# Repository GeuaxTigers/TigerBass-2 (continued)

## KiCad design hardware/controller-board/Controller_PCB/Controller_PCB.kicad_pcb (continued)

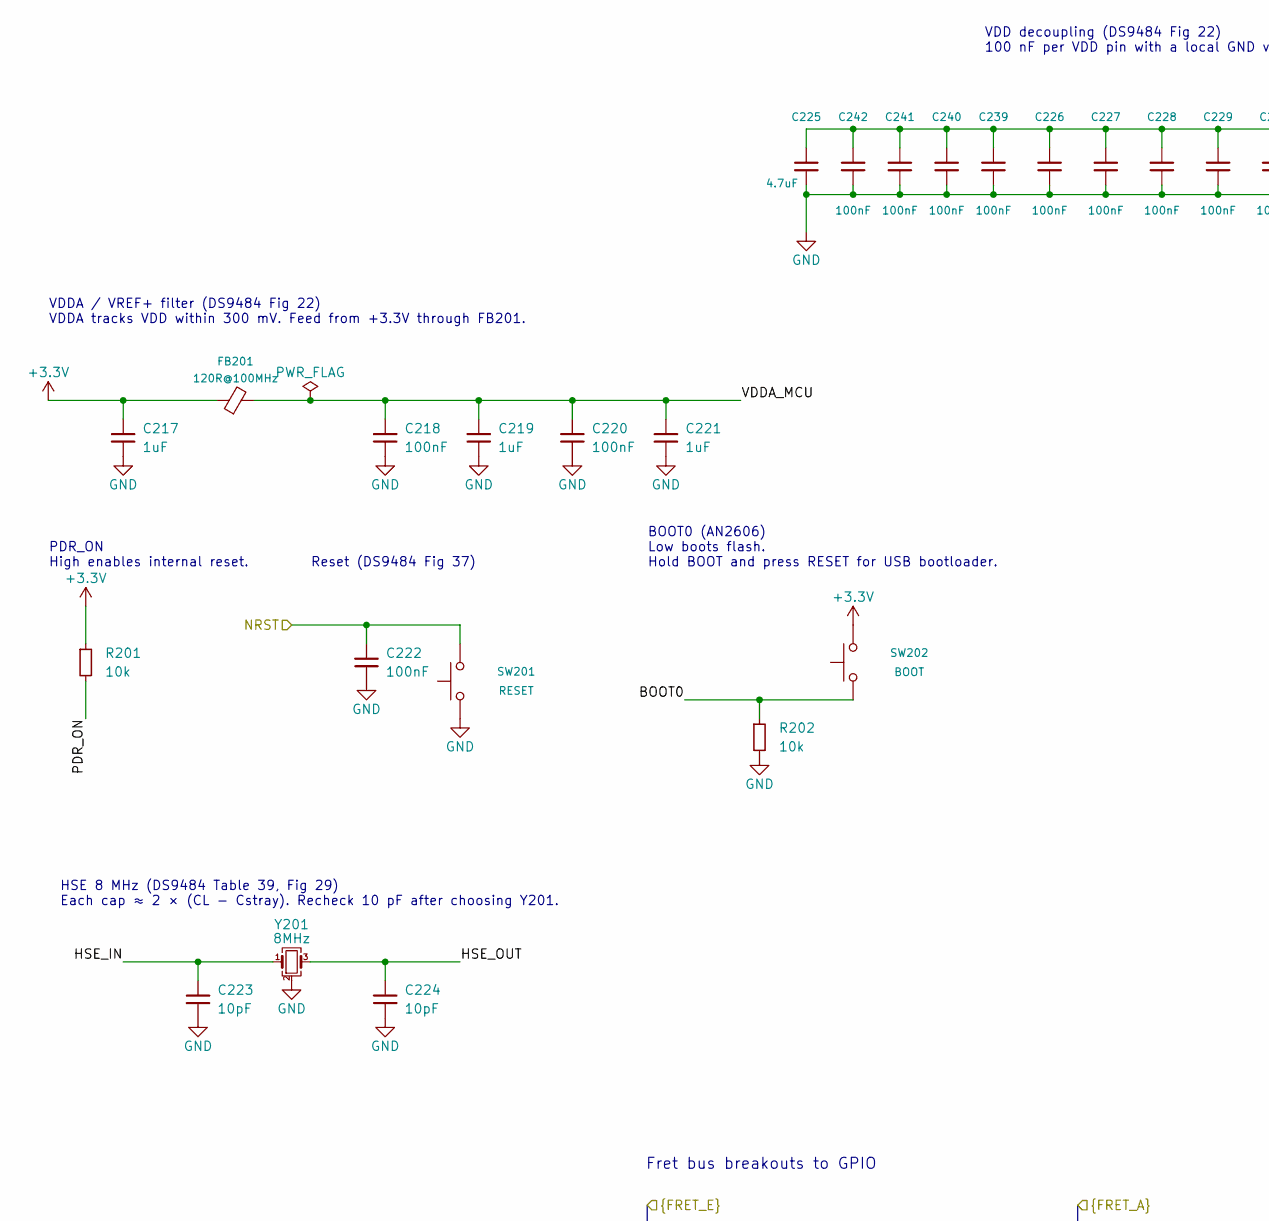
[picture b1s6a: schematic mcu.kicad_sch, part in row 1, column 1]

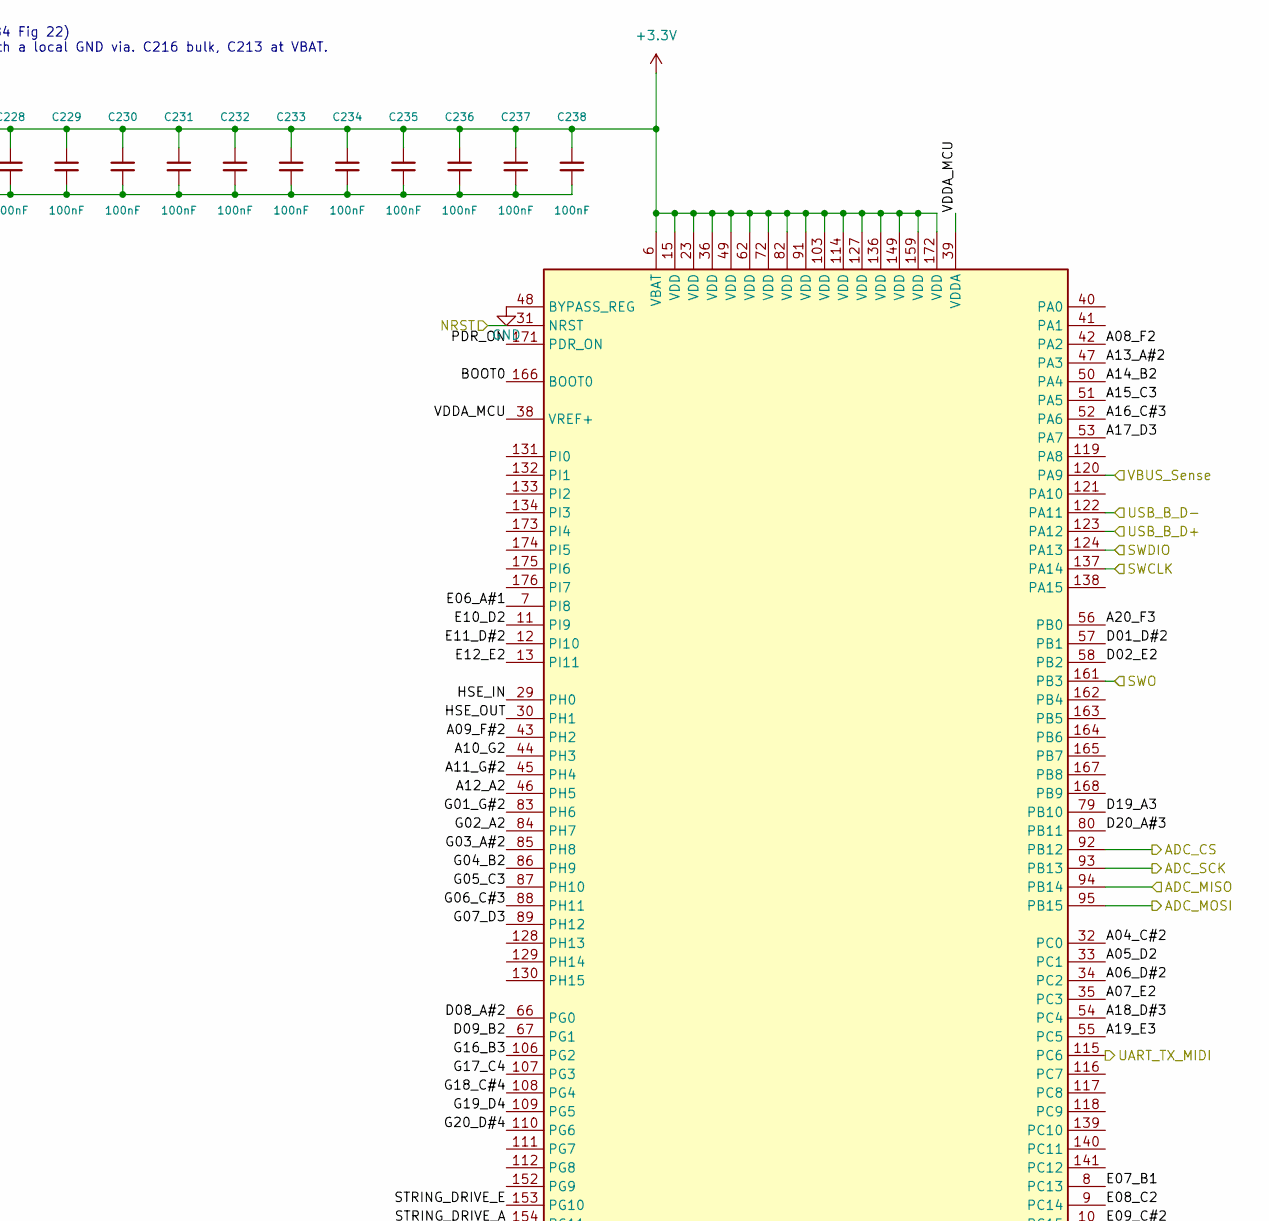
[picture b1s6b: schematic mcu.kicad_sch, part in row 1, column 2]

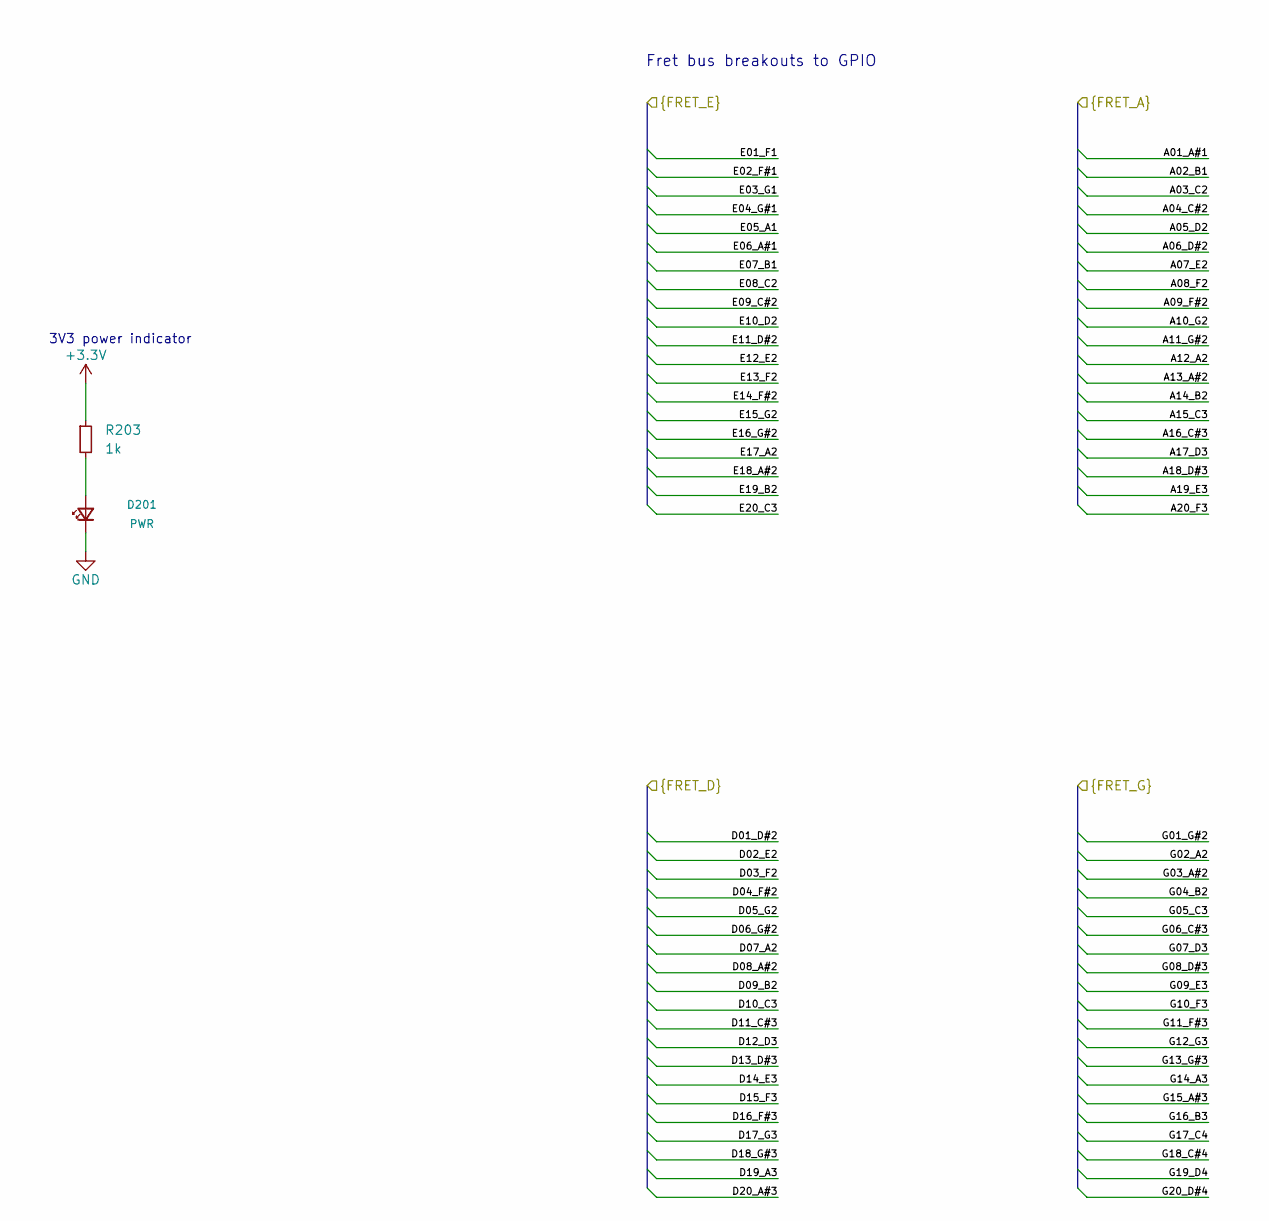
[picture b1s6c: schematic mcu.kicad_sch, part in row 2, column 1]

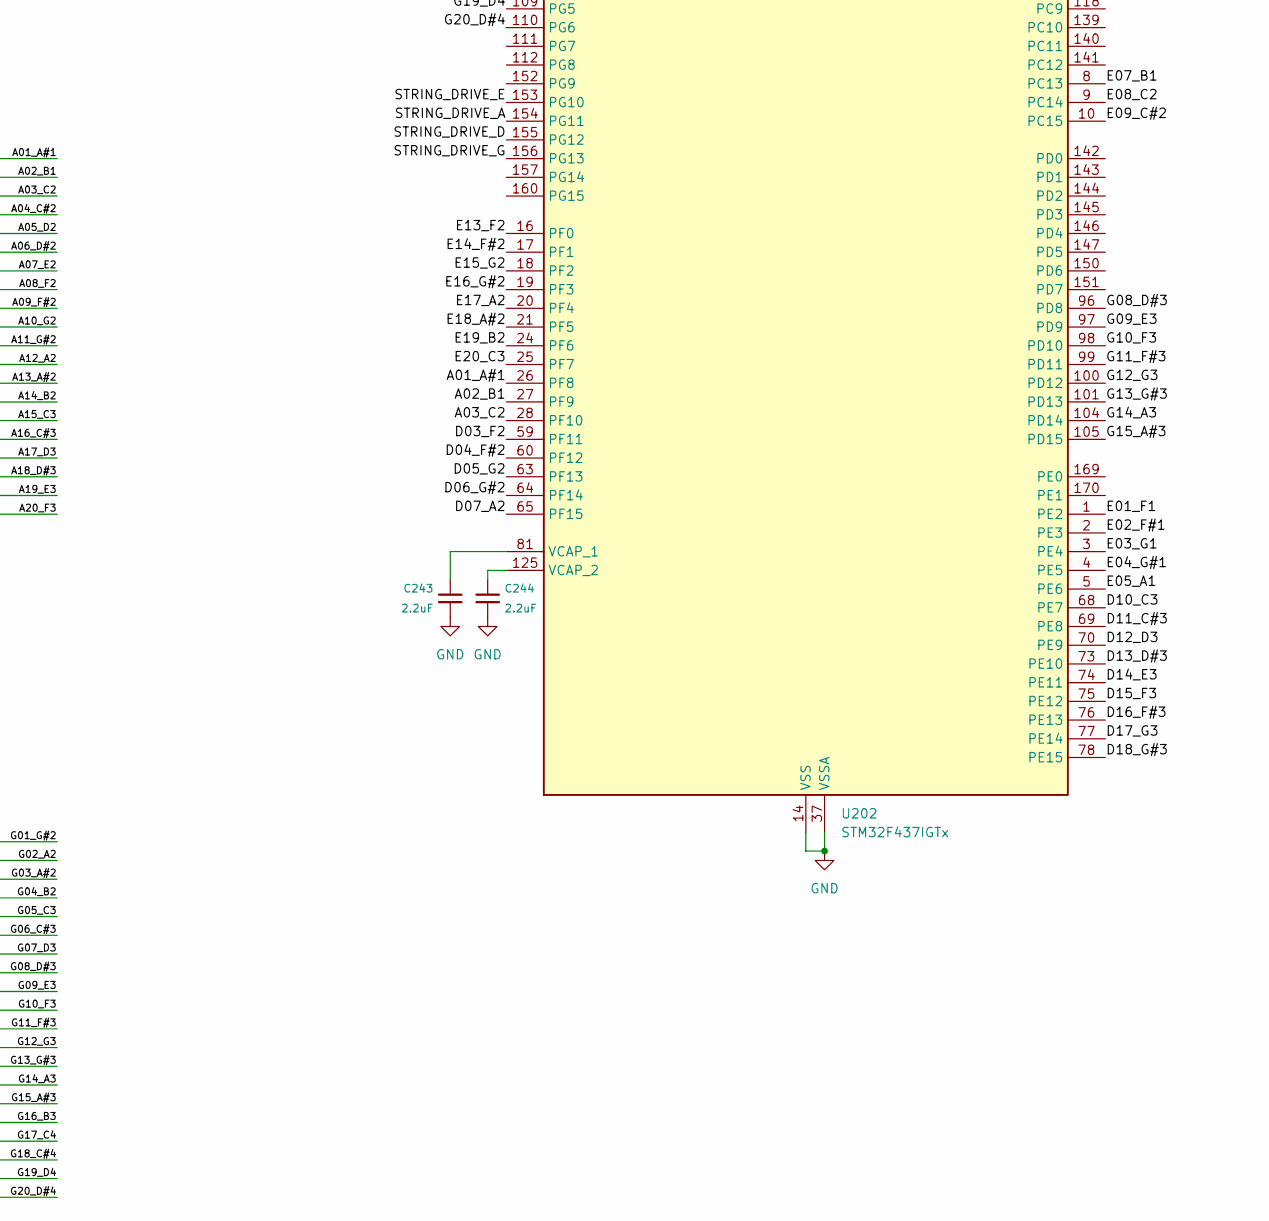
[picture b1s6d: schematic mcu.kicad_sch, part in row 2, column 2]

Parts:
C217, C219, C221: 1uF; C_0603_1608Metric
C218, C220, C222, C226, C227, C228, C229, C230, C231, C232, C233, C234, C235, C236, C237, C238, C239, C240, C241, C242: 100nF; C_0603_1608Metric
C223, C224: 10pF; C_0603_1608Metric
C225: 4.7uF; C_0603_1608Metric
C243, C244: 2.2uF; C_0603_1608Metric
D201: PWR; LED_0603_1608Metric
FB201: 120R@100MHz; L_0603_1608Metric
R201, R202: 10k; R_0603_1608Metric
R203: 1k; R_0603_1608Metric
SW201: RESET; SW_SPST_TL3342
SW202: BOOT; SW_SPST_TL3342
U202: STM32F437IGTx; LQFP-176_24x24mm_P0.5mm
Y201: 8MHz; Crystal_SMD_3225-4Pin_3.2x2.5mm

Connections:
+3.3V: C217.1, C225.1, C226.1, C227.1, C228.1, C229.1, C230.1, C231.1, C232.1, C233.1, C234.1, C235.1, C236.1, C237.1, C238.1, C239.1, C240.1, C241.1, C242.1, FB201.1, R201.1, R203.1, SW202.2, U202.6 (VBAT), U202.15 (VDD), U202.23 (VDD), U202.36 (VDD), U202.49 (VDD), U202.62 (VDD), U202.72 (VDD), U202.82 (VDD), U202.91 (VDD), U202.103 (VDD), U202.114 (VDD), U202.127 (VDD), U202.136 (VDD), U202.149 (VDD), U202.159 (VDD), U202.172 (VDD); also elsewhere on the board
/A01_A#1: U202.26 (PF8); also elsewhere on the board
/A02_B1: U202.27 (PF9); also elsewhere on the board
/A03_C2: U202.28 (PF10); also elsewhere on the board
/A04_C#2: U202.32 (PC0); also elsewhere on the board
/A05_D2: U202.33 (PC1); also elsewhere on the board
/A06_D#2: U202.34 (PC2); also elsewhere on the board
/A07_E2: U202.35 (PC3); also elsewhere on the board
/A08_F2: U202.42 (PA2); also elsewhere on the board
/A09_F#2: U202.43 (PH2); also elsewhere on the board
/A10_G2: U202.44 (PH3); also elsewhere on the board
/A11_G#2: U202.45 (PH4); also elsewhere on the board
/A12_A2: U202.46 (PH5); also elsewhere on the board
/A13_A#2: U202.47 (PA3); also elsewhere on the board
/A14_B2: U202.50 (PA4); also elsewhere on the board
/A15_C3: U202.51 (PA5); also elsewhere on the board
/A16_C#3: U202.52 (PA6); also elsewhere on the board
/A17_D3: U202.53 (PA7); also elsewhere on the board
/A18_D#3: U202.54 (PC4); also elsewhere on the board
/A19_E3: U202.55 (PC5); also elsewhere on the board
/A20_F3: U202.56 (PB0); also elsewhere on the board
/Amplitude Detection/ADC_CS: U202.92 (PB12)
/Amplitude Detection/ADC_MISO: U202.94 (PB14)
/Amplitude Detection/ADC_MOSI: U202.95 (PB15)
/Amplitude Detection/ADC_SCK: U202.93 (PB13)
/D01_D#2: U202.57 (PB1); also elsewhere on the board
/D02_E2: U202.58 (PB2); also elsewhere on the board
/D03_F2: U202.59 (PF11); also elsewhere on the board
/D04_F#2: U202.60 (PF12); also elsewhere on the board
/D05_G2: U202.63 (PF13); also elsewhere on the board
/D06_G#2: U202.64 (PF14); also elsewhere on the board
/D07_A2: U202.65 (PF15); also elsewhere on the board
/D08_A#2: U202.66 (PG0); also elsewhere on the board
/D09_B2: U202.67 (PG1); also elsewhere on the board
/D10_C3: U202.68 (PE7); also elsewhere on the board
/D11_C#3: U202.69 (PE8); also elsewhere on the board
/D12_D3: U202.70 (PE9); also elsewhere on the board
/D13_D#3: U202.73 (PE10); also elsewhere on the board
/D14_E3: U202.74 (PE11); also elsewhere on the board
/D15_F3: U202.75 (PE12); also elsewhere on the board
/D16_F#3: U202.76 (PE13); also elsewhere on the board
/D17_G3: U202.77 (PE14); also elsewhere on the board
/D18_G#3: U202.78 (PE15); also elsewhere on the board
/D19_A3: U202.79 (PB10); also elsewhere on the board
/D20_A#3: U202.80 (PB11); also elsewhere on the board
/E01_F1: U202.1 (PE2); also elsewhere on the board
/E02_F#1: U202.2 (PE3); also elsewhere on the board
/E03_G1: U202.3 (PE4); also elsewhere on the board
/E04_G#1: U202.4 (PE5); also elsewhere on the board
/E05_A1: U202.5 (PE6); also elsewhere on the board
/E06_A#1: U202.7 (PI8); also elsewhere on the board
/E07_B1: U202.8 (PC13); also elsewhere on the board
/E08_C2: U202.9 (PC14); also elsewhere on the board
/E09_C#2: U202.10 (PC15); also elsewhere on the board
/E10_D2: U202.11 (PI9); also elsewhere on the board
/E11_D#2: U202.12 (PI10); also elsewhere on the board
/E12_E2: U202.13 (PI11); also elsewhere on the board
/E13_F2: U202.16 (PF0); also elsewhere on the board
/E14_F#2: U202.17 (PF1); also elsewhere on the board
/E15_G2: U202.18 (PF2); also elsewhere on the board
/E16_G#2: U202.19 (PF3); also elsewhere on the board
/E17_A2: U202.20 (PF4); also elsewhere on the board
/E18_A#2: U202.21 (PF5); also elsewhere on the board
/E19_B2: U202.24 (PF6); also elsewhere on the board
/E20_C3: U202.25 (PF7); also elsewhere on the board
/G01_G#2: U202.83 (PH6); also elsewhere on the board
/G02_A2: U202.84 (PH7); also elsewhere on the board
/G03_A#2: U202.85 (PH8); also elsewhere on the board
/G04_B2: U202.86 (PH9); also elsewhere on the board
/G05_C3: U202.87 (PH10); also elsewhere on the board
/G06_C#3: U202.88 (PH11); also elsewhere on the board
/G07_D3: U202.89 (PH12); also elsewhere on the board
/G08_D#3: U202.96 (PD8); also elsewhere on the board
/G09_E3: U202.97 (PD9); also elsewhere on the board
/G10_F3: U202.98 (PD10); also elsewhere on the board
/G11_F#3: U202.99 (PD11); also elsewhere on the board
/G12_G3: U202.100 (PD12); also elsewhere on the board
/G13_G#3: U202.101 (PD13); also elsewhere on the board
/G14_A3: U202.104 (PD14); also elsewhere on the board
/G15_A#3: U202.105 (PD15); also elsewhere on the board
/G16_B3: U202.106 (PG2); also elsewhere on the board
/G17_C4: U202.107 (PG3); also elsewhere on the board
/G18_C#4: U202.108 (PG4); also elsewhere on the board
/G19_D4: U202.109 (PG5); also elsewhere on the board
/G20_D#4: U202.110 (PG6); also elsewhere on the board
/MCU/BOOT0: R202.1, SW202.1, U202.166 (BOOT0)
/MCU/HSE_IN: C223.1, U202.29 (PH0), Y201.1
/MCU/HSE_OUT: C224.1, U202.30 (PH1), Y201.3
/MCU/PDR_ON: R201.2, U202.171 (PDR_ON)
/MCU/STRING_DRIVE_A: U202.154 (PG11)
/MCU/STRING_DRIVE_D: U202.155 (PG12)
/MCU/STRING_DRIVE_E: U202.153 (PG10)
/MCU/STRING_DRIVE_G: U202.156 (PG13)
/MCU/VDDA_MCU: C218.1, C219.1, C220.1, C221.1, FB201.2, U202.38 (VREF+), U202.39 (VDDA)
/NRST: C222.1, SW201.2, U202.31 (NRST); also elsewhere on the board
/SWCLK: U202.137 (PA14); also elsewhere on the board
/SWDIO: U202.124 (PA13); also elsewhere on the board
/SWO: U202.161 (PB3); also elsewhere on the board
/UART_TX_MIDI: U202.115 (PC6)
/USB_B_D+: U202.123 (PA12); also elsewhere on the board
/USB_B_D-: U202.122 (PA11); also elsewhere on the board
/VBUS_Sense: U202.120 (PA9); also elsewhere on the board
GND: C217.2, C218.2, C219.2, C220.2, C221.2, C222.2, C223.2, C224.2, C225.2, C226.2, C227.2, C228.2, C229.2, C230.2, C231.2, C232.2, C233.2, C234.2, C235.2, C236.2, C237.2, C238.2, C239.2, C240.2, C241.2, C242.2, C243.2, C244.2, D201.1 (K), R202.2, SW201.1, U202.14 (VSS), U202.22 (VSS), U202.37 (VSSA), U202.48 (BYPASS_REG), U202.61 (VSS), U202.71 (VSS), U202.90 (VSS), U202.102 (VSS), U202.113 (VSS), U202.126 (VSS), U202.135 (VSS), U202.148 (VSS), U202.158 (VSS), Y201.2 (G), Y201.4 (G); also elsewhere on the board
unnamed: D201.2 (A), R203.2
unnamed: C243.1, U202.81 (VCAP_1)
unnamed: C244.1, U202.125 (VCAP_2)

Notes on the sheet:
VDD decoupling (DS9484 Fig 22) 100 nF per VDD pin with a local GND via. C216 bulk, C213 at VBAT.
HSE 8 MHz (DS9484 Table 39, Fig 29) Each cap ≈ 2 × (CL − Cstray). Recheck 10 pF after choosing Y201.
Reset (DS9484 Fig 37)
Fret bus breakouts to GPIO
PDR_ON High enables internal reset.
VDDA / VREF+ filter (DS9484 Fig 22) VDDA tracks VDD within 300 mV. Feed from +3.3V through FB201.
BOOT0 (AN2606) Low boots flash. Hold BOOT and press RESET for USB bootloader.
3V3 power indicator

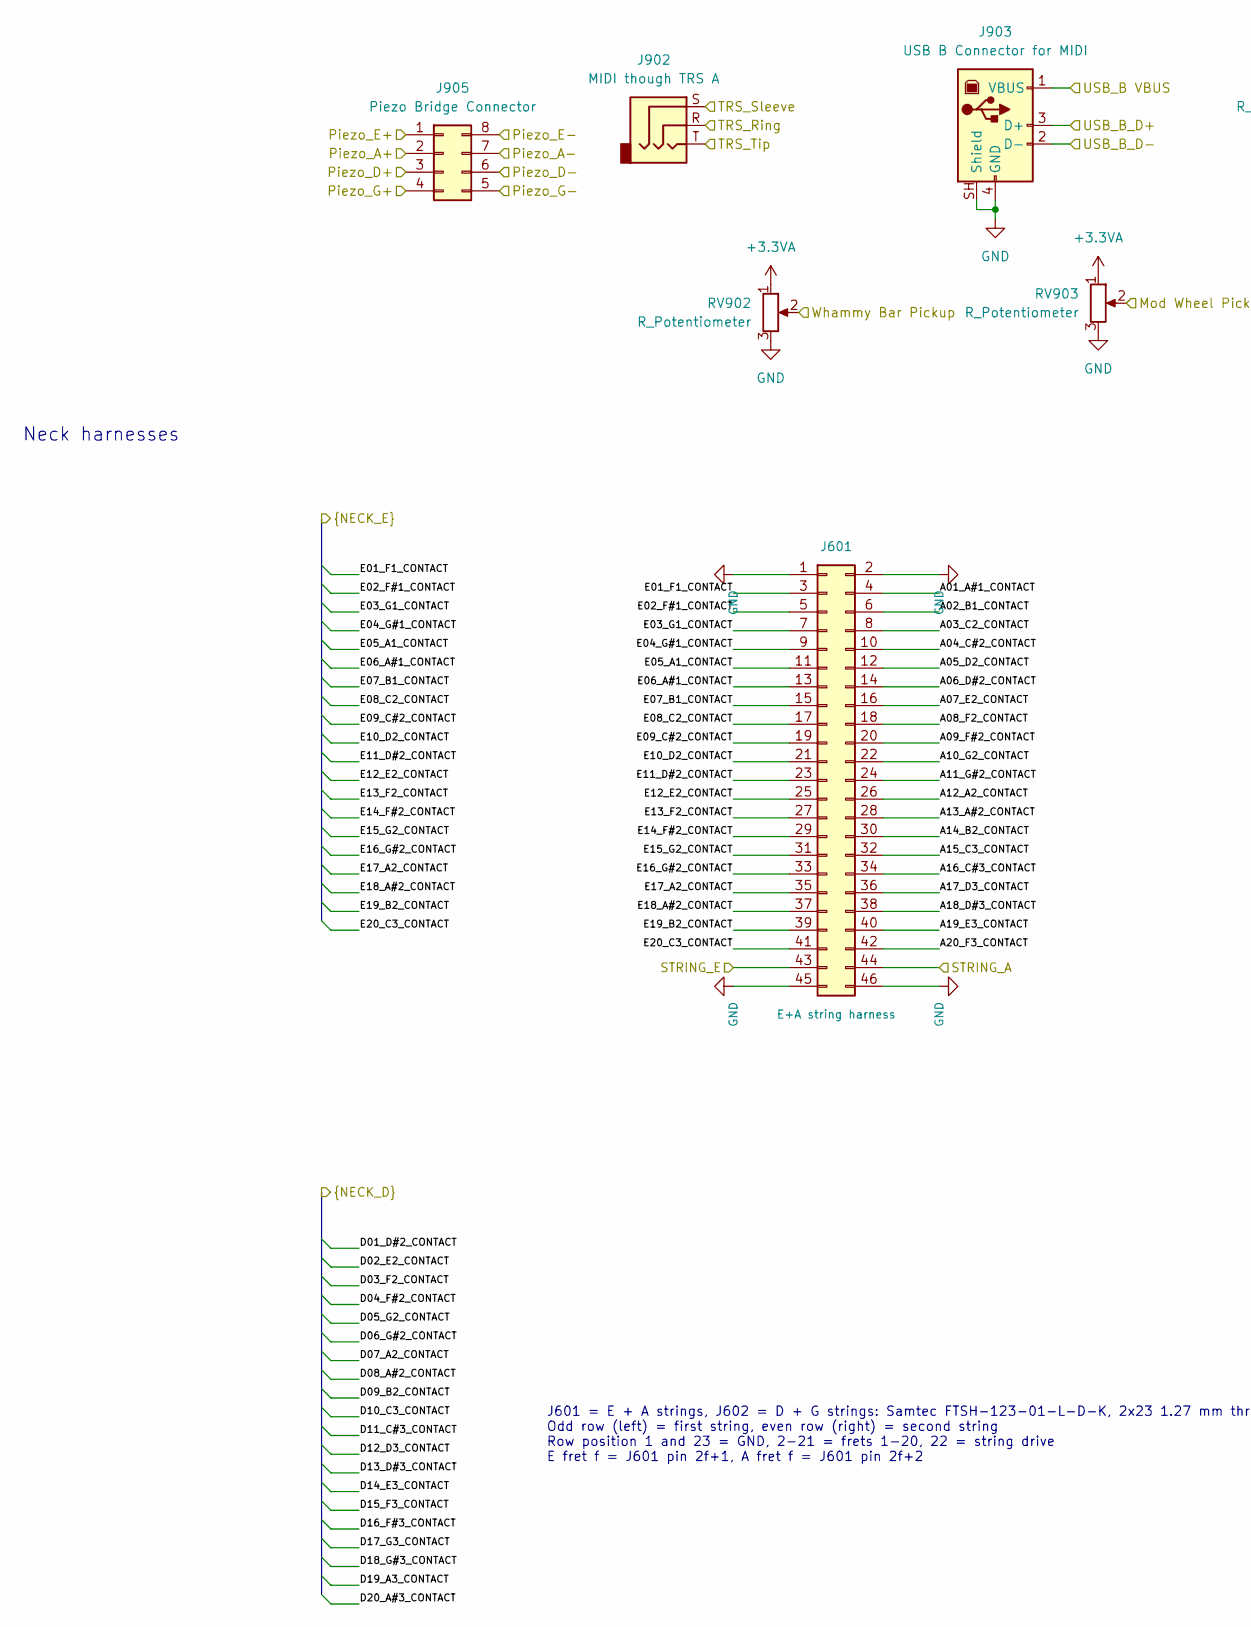
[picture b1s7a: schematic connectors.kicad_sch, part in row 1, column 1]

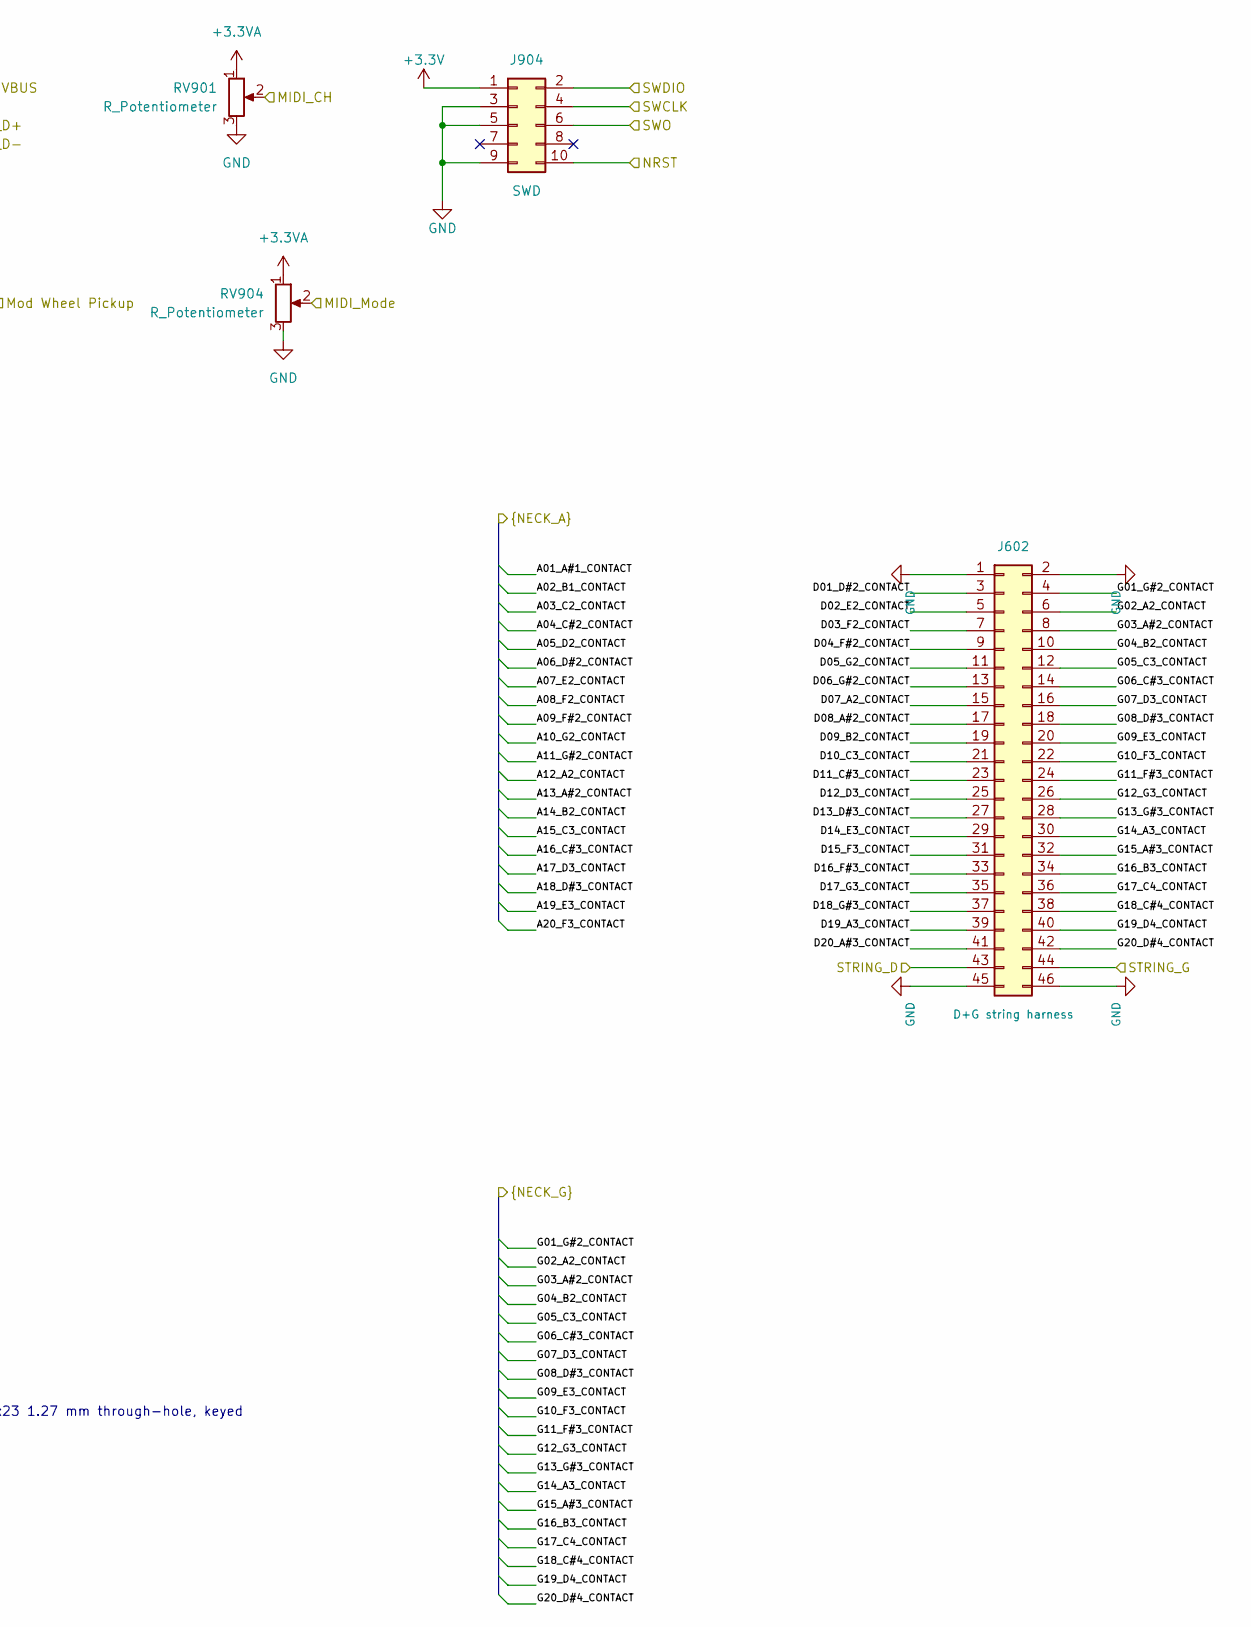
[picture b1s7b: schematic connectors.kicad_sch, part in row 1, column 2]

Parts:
J601: E+A string harness; PinHeader_2x23_P1.27mm_Vertical
J602: D+G string harness; PinHeader_2x23_P1.27mm_Vertical
J902: MIDI though TRS A
J903: USB B Connector for MIDI
J904: SWD; PinHeader_2x05_P1.27mm_Vertical_SMD
J905: Piezo Bridge Connector
RV901, RV902, RV903, RV904: R_Potentiometer

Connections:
+3.3V: J904.1; also elsewhere on the board
/A01_A#1_CONTACT: J601.4; also elsewhere on the board
/A02_B1_CONTACT: J601.6; also elsewhere on the board
/A03_C2_CONTACT: J601.8; also elsewhere on the board
/A04_C#2_CONTACT: J601.10; also elsewhere on the board
/A05_D2_CONTACT: J601.12; also elsewhere on the board
/A06_D#2_CONTACT: J601.14; also elsewhere on the board
/A07_E2_CONTACT: J601.16; also elsewhere on the board
/A08_F2_CONTACT: J601.18; also elsewhere on the board
/A09_F#2_CONTACT: J601.20; also elsewhere on the board
/A10_G2_CONTACT: J601.22; also elsewhere on the board
/A11_G#2_CONTACT: J601.24; also elsewhere on the board
/A12_A2_CONTACT: J601.26; also elsewhere on the board
/A13_A#2_CONTACT: J601.28; also elsewhere on the board
/A14_B2_CONTACT: J601.30; also elsewhere on the board
/A15_C3_CONTACT: J601.32; also elsewhere on the board
/A16_C#3_CONTACT: J601.34; also elsewhere on the board
/A17_D3_CONTACT: J601.36; also elsewhere on the board
/A18_D#3_CONTACT: J601.38; also elsewhere on the board
/A19_E3_CONTACT: J601.40; also elsewhere on the board
/A20_F3_CONTACT: J601.42; also elsewhere on the board
/D01_D#2_CONTACT: J602.3; also elsewhere on the board
/D02_E2_CONTACT: J602.5; also elsewhere on the board
/D03_F2_CONTACT: J602.7; also elsewhere on the board
/D04_F#2_CONTACT: J602.9; also elsewhere on the board
/D05_G2_CONTACT: J602.11; also elsewhere on the board
/D06_G#2_CONTACT: J602.13; also elsewhere on the board
/D07_A2_CONTACT: J602.15; also elsewhere on the board
/D08_A#2_CONTACT: J602.17; also elsewhere on the board
/D09_B2_CONTACT: J602.19; also elsewhere on the board
/D10_C3_CONTACT: J602.21; also elsewhere on the board
/D11_C#3_CONTACT: J602.23; also elsewhere on the board
/D12_D3_CONTACT: J602.25; also elsewhere on the board
/D13_D#3_CONTACT: J602.27; also elsewhere on the board
/D14_E3_CONTACT: J602.29; also elsewhere on the board
/D15_F3_CONTACT: J602.31; also elsewhere on the board
/D16_F#3_CONTACT: J602.33; also elsewhere on the board
/D17_G3_CONTACT: J602.35; also elsewhere on the board
/D18_G#3_CONTACT: J602.37; also elsewhere on the board
/D19_A3_CONTACT: J602.39; also elsewhere on the board
/D20_A#3_CONTACT: J602.41; also elsewhere on the board
/E01_F1_CONTACT: J601.3; also elsewhere on the board
/E02_F#1_CONTACT: J601.5; also elsewhere on the board
/E03_G1_CONTACT: J601.7; also elsewhere on the board
/E04_G#1_CONTACT: J601.9; also elsewhere on the board
/E05_A1_CONTACT: J601.11; also elsewhere on the board
/E06_A#1_CONTACT: J601.13; also elsewhere on the board
/E07_B1_CONTACT: J601.15; also elsewhere on the board
/E08_C2_CONTACT: J601.17; also elsewhere on the board
/E09_C#2_CONTACT: J601.19; also elsewhere on the board
/E10_D2_CONTACT: J601.21; also elsewhere on the board
/E11_D#2_CONTACT: J601.23; also elsewhere on the board
/E12_E2_CONTACT: J601.25; also elsewhere on the board
/E13_F2_CONTACT: J601.27; also elsewhere on the board
/E14_F#2_CONTACT: J601.29; also elsewhere on the board
/E15_G2_CONTACT: J601.31; also elsewhere on the board
/E16_G#2_CONTACT: J601.33; also elsewhere on the board
/E17_A2_CONTACT: J601.35; also elsewhere on the board
/E18_A#2_CONTACT: J601.37; also elsewhere on the board
/E19_B2_CONTACT: J601.39; also elsewhere on the board
/E20_C3_CONTACT: J601.41; also elsewhere on the board
/G01_G#2_CONTACT: J602.4; also elsewhere on the board
/G02_A2_CONTACT: J602.6; also elsewhere on the board
/G03_A#2_CONTACT: J602.8; also elsewhere on the board
/G04_B2_CONTACT: J602.10; also elsewhere on the board
/G05_C3_CONTACT: J602.12; also elsewhere on the board
/G06_C#3_CONTACT: J602.14; also elsewhere on the board
/G07_D3_CONTACT: J602.16; also elsewhere on the board
/G08_D#3_CONTACT: J602.18; also elsewhere on the board
/G09_E3_CONTACT: J602.20; also elsewhere on the board
/G10_F3_CONTACT: J602.22; also elsewhere on the board
/G11_F#3_CONTACT: J602.24; also elsewhere on the board
/G12_G3_CONTACT: J602.26; also elsewhere on the board
/G13_G#3_CONTACT: J602.28; also elsewhere on the board
/G14_A3_CONTACT: J602.30; also elsewhere on the board
/G15_A#3_CONTACT: J602.32; also elsewhere on the board
/G16_B3_CONTACT: J602.34; also elsewhere on the board
/G17_C4_CONTACT: J602.36; also elsewhere on the board
/G18_C#4_CONTACT: J602.38; also elsewhere on the board
/G19_D4_CONTACT: J602.40; also elsewhere on the board
/G20_D#4_CONTACT: J602.42; also elsewhere on the board
/NRST: J904.10; also elsewhere on the board
/STRING_A: J601.44; also elsewhere on the board
/STRING_D: J602.43; also elsewhere on the board
/STRING_E: J601.43; also elsewhere on the board
/STRING_G: J602.44; also elsewhere on the board
/SWCLK: J904.4; also elsewhere on the board
/SWDIO: J904.2; also elsewhere on the board
/SWO: J904.6; also elsewhere on the board
GND: J601.1, J601.2, J601.45, J601.46, J602.1, J602.2, J602.45, J602.46, J903.4 (GND), J903.SH (Shield), J904.3, J904.5, J904.9, RV901.3, RV902.3, RV903.3, RV904.3; also elsewhere on the board
unnamed: RV901.1, RV902.1, RV903.1, RV904.1

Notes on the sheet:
J601 = E + A strings, J602 = D + G strings: Samtec FTSH-123-01-L-D-K, 2x23 1.27 mm through-hole, keyed Odd row (left) = first string, even row (right) = second string Row position 1 and 23 = GND, 2-21 = frets 1-20, 22 = string drive E fret f = J601 pin 2f+1, A fret f = J601 pin 2f+2
Neck harnesses

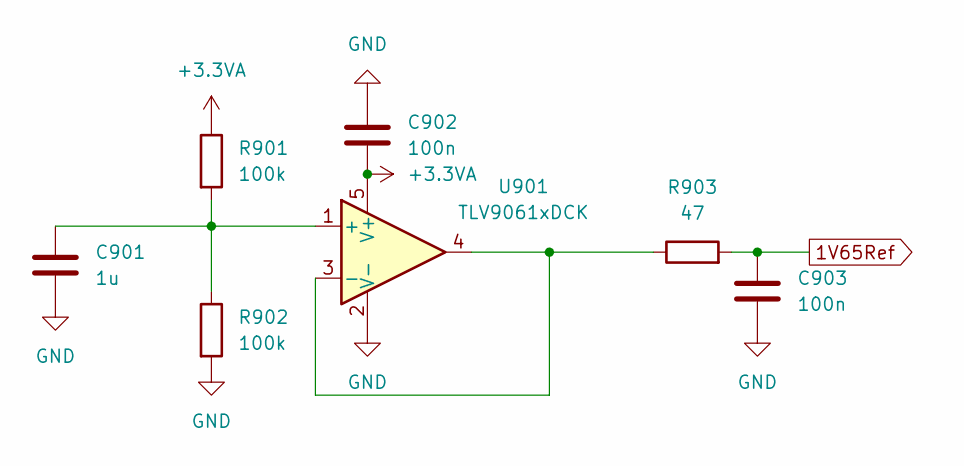
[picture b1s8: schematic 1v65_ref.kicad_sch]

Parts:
C901: 1u; C_0402_1005Metric
C902, C903: 100n; C_0402_1005Metric
R901, R902: 100k; R_0402_1005Metric
R903: 47; R_0402_1005Metric
U901: TLV9061xDCK; SOT-353_SC-70-5

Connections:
1V65Ref: C903.1, R903.2; also elsewhere on the board
+3.3VA: C902.2, R901.1, U901.5 (V+); also elsewhere on the board
GND: C901.2, C902.1, C903.2, R902.2, U901.2 (V-); also elsewhere on the board
unnamed: C901.1, R901.2, R902.1, U901.1 (+)
unnamed: R903.1, U901.3 (-), U901.4

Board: 2 copper layers, 187 parts (0 on the bottom side), 209 nets, no tracks yet.

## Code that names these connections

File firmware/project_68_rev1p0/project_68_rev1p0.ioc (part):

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Mcu.Name=STM32F437I(G-I)Tx
Mcu.Package=LQFP176
Mcu.UserName=STM32F437IGTx
PA0/WKUP.GPIOParameters=GPIO_Label
PA0/WKUP.GPIO_Label=ADC_String_1
PA0/WKUP.Signal=ADCx_IN0
PA1.GPIOParameters=GPIO_Label
PA1.GPIO_Label=ADC_String_2
PA1.Signal=ADCx_IN1
PA10.GPIOParameters=GPIO_PuPd,GPIO_Label
PA10.GPIO_Label=input_46
PA10.GPIO_PuPd=GPIO_PULLDOWN
PA10.Signal=GPIO_Input
PA11.GPIOParameters=GPIO_Label
PA11.GPIO_Label=USB_M
PA11.Mode=Device_Only
PA11.Signal=USB_OTG_FS_DM
PA12.GPIOParameters=GPIO_Label
PA12.GPIO_Label=USB_P
PA12.Mode=Device_Only
PA12.Signal=USB_OTG_FS_DP
PA13.GPIOParameters=GPIO_Label
PA13.GPIO_Label=SWDIO
PA13.Mode=Trace_Asynchronous_SW
PA13.Signal=SYS_JTMS-SWDIO
PA14.GPIOParameters=GPIO_Label
PA14.GPIO_Label=SWCLK
PA14.Mode=Trace_Asynchronous_SW
PA14.Signal=SYS_JTCK-SWCLK
PA15.GPIOParameters=GPIO_PuPd,GPIO_Label
PA15.GPIO_Label=input_75
PA15.GPIO_PuPd=GPIO_PULLDOWN
PA15.Signal=GPIO_Input
PA2.GPIOParameters=GPIO_Label
PA2.GPIO_Label=ADC_String_3
PA2.Signal=ADCx_IN2
PA3.GPIOParameters=GPIO_Label
PA3.GPIO_Label=ADC_String_4
PA3.Signal=ADCx_IN3
PA4.GPIOParameters=GPIO_Label
PA4.GPIO_Label=ADC_Octave
PA4.Signal=ADCx_IN4
PA5.GPIOParameters=GPIO_Label
PA5.GPIO_Label=ADC_Mode
PA5.Signal=ADCx_IN5
PA6.GPIOParameters=GPIO_Label
PA6.GPIO_Label=ADC_Bend
PA6.Signal=ADCx_IN6
PA7.GPIOParameters=GPIO_Label
PA7.GPIO_Label=ADC_MIDI_Ch
PA7.Signal=ADCx_IN7
PA8.GPIOParameters=GPIO_PuPd,GPIO_Label
PA8.GPIO_Label=input_74
PA8.GPIO_PuPd=GPIO_PULLDOWN
PA8.Signal=GPIO_Input
PA9.GPIOParameters=GPIO_Label
PA9.GPIO_Label=VBUS_Sense
PA9.Signal=GPXTI9
PB0.GPIOParameters=GPIO_Label
PB0.GPIO_Label=ADC_Slider
PB0.Signal=ADCx_IN8
PB10.GPIOParameters=GPIO_PuPd,GPIO_Label
PB10.GPIO_Label=input_66
PB10.GPIO_PuPd=GPIO_PULLDOWN
PB10.Signal=GPIO_Input
PB11.GPIOParameters=GPIO_PuPd,GPIO_Label
PB11.GPIO_Label=input_54
PB11.GPIO_PuPd=GPIO_PULLDOWN
PB11.Signal=GPIO_Input
PB12.GPIOParameters=GPIO_PuPd,GPIO_Label
PB12.GPIO_Label=input_67
PB12.GPIO_PuPd=GPIO_PULLDOWN
PB12.Signal=GPIO_Input
PB14.GPIOParameters=GPIO_PuPd,GPIO_Label
PB14.GPIO_Label=input_53
PB14.GPIO_PuPd=GPIO_PULLDOWN
PB14.Signal=GPIO_Input
PB15.GPIOParameters=GPIO_PuPd,GPIO_Label
PB15.GPIO_Label=input_68
PB15.GPIO_PuPd=GPIO_PULLDOWN
PB15.Signal=GPIO_Input
PB3.GPIOParameters=GPIO_Label
PB3.GPIO_Label=SWO
PB3.Mode=Trace_Asynchronous_SW
PB3.Signal=SYS_JTDO-SWO
PB4.GPIOParameters=GPIO_PuPd,GPIO_Label
PB4.GPIO_Label=input_22
PB4.GPIO_PuPd=GPIO_PULLDOWN
PB4.Signal=GPIO_Input
PB5.GPIOParameters=GPIO_PuPd,GPIO_Label
PB5.GPIO_Label=input_18
PB5.GPIO_PuPd=GPIO_PULLDOWN
PB5.Signal=GPIO_Input
PB6.GPIOParameters=GPIO_PuPd,GPIO_Label
PB6.GPIO_Label=input_23
PB6.GPIO_PuPd=GPIO_PULLDOWN
PB6.Signal=GPIO_Input
PB7.GPIOParameters=GPIO_PuPd,GPIO_Label
PB7.GPIO_Label=input_17
PB7.GPIO_PuPd=GPIO_PULLDOWN
PB7.Signal=GPIO_Input
PB8.GPIOParameters=GPIO_PuPd,GPIO_Label
PB8.GPIO_Label=input_16
PB8.GPIO_PuPd=GPIO_PULLDOWN
PB8.Signal=GPIO_Input
PB9.GPIOParameters=GPIO_PuPd,GPIO_Label
PB9.GPIO_Label=input_24
PB9.GPIO_PuPd=GPIO_PULLDOWN
PB9.Signal=GPIO_Input
PC1.GPIOParameters=GPIO_PuPd,GPIO_Label
PC1.GPIO_Label=input_31
PC1.GPIO_PuPd=GPIO_PULLDOWN
PC1.Signal=GPIO_Input
PC10.GPIOParameters=GPIO_PuPd,GPIO_Label
PC10.GPIO_Label=input_45
PC10.GPIO_PuPd=GPIO_PULLDOWN
PC10.Signal=GPIO_Input
PC11.GPIOParameters=GPIO_PuPd,GPIO_Label
PC11.GPIO_Label=input_76
PC11.GPIO_PuPd=GPIO_PULLDOWN
PC11.Signal=GPIO_Input
PC12.GPIOParameters=GPIO_PuPd,GPIO_Label
PC12.GPIO_Label=input_44
PC12.GPIO_PuPd=GPIO_PULLDOWN
PC12.Signal=GPIO_Input
PC13.GPIOParameters=GPIO_PuPd,GPIO_Label
PC13.GPIO_Label=input_14
PC13.GPIO_PuPd=GPIO_PULLDOWN
PC13.Signal=GPIO_Input
PC14/OSC32_IN.GPIOParameters=GPIO_PuPd,GPIO_Label
PC14/OSC32_IN.GPIO_Label=input_27
PC14/OSC32_IN.GPIO_PuPd=GPIO_PULLDOWN
PC14/OSC32_IN.Signal=GPIO_Input
PC15/OSC32_OUT.GPIOParameters=GPIO_PuPd,GPIO_Label
PC15/OSC32_OUT.GPIO_Label=input_3
PC15/OSC32_OUT.GPIO_PuPd=GPIO_PULLDOWN
PC15/OSC32_OUT.Signal=GPIO_Input
PC2.GPIOParameters=GPIO_PuPd,GPIO_Label
PC2.GPIO_Label=input_9
PC2.GPIO_PuPd=GPIO_PULLDOWN
PC2.Signal=GPIO_Input
PC3.GPIOParameters=GPIO_PuPd,GPIO_Label
PC3.GPIO_Label=input_32
PC3.GPIO_PuPd=GPIO_PULLDOWN
PC3.Signal=GPIO_Input
PC4.GPIOParameters=GPIO_PuPd,GPIO_Label
PC4.GPIO_Label=input_8
PC4.GPIO_PuPd=GPIO_PULLDOWN
PC4.Signal=GPIO_Input
PC5.GPIOParameters=GPIO_PuPd,GPIO_Label
PC5.GPIO_Label=input_33
PC5.GPIO_PuPd=GPIO_PULLDOWN
PC5.Signal=GPIO_Input
PC6.GPIOParameters=GPIO_PuPd,GPIO_Label
PC6.GPIO_Label=input_48
PC6.GPIO_PuPd=GPIO_PULLDOWN
PC6.Signal=GPIO_Input
PC8.GPIOParameters=GPIO_PuPd,GPIO_Label
PC8.GPIO_Label=input_73
PC8.GPIO_PuPd=GPIO_PULLDOWN
PC8.Signal=GPIO_Input
PC9.GPIOParameters=GPIO_PuPd,GPIO_Label
PC9.GPIO_Label=input_47
PC9.GPIO_PuPd=GPIO_PULLDOWN
PC9.Signal=GPIO_Input
PD0.GPIOParameters=GPIO_PuPd,GPIO_Label
PD0.GPIO_Label=input_77
PD0.GPIO_PuPd=GPIO_PULLDOWN
PD0.Signal=GPIO_Input
PD1.GPIOParameters=GPIO_PuPd,GPIO_Label
PD1.GPIO_Label=input_43
PD1.GPIO_PuPd=GPIO_PULLDOWN
PD1.Signal=GPIO_Input
PD13.GPIOParameters=GPIO_PuPd,GPIO_Label
PD13.GPIO_Label=input_69
PD13.GPIO_PuPd=GPIO_PULLDOWN
PD13.Signal=GPIO_Input
PD14.GPIOParameters=GPIO_PuPd,GPIO_Label
PD14.GPIO_Label=input_51
PD14.GPIO_PuPd=GPIO_PULLDOWN
PD14.Signal=GPIO_Input
PD15.GPIOParameters=GPIO_PuPd,GPIO_Label
PD15.GPIO_Label=input_70
PD15.GPIO_PuPd=GPIO_PULLDOWN
PD15.Signal=GPIO_Input
PD2.GPIOParameters=GPIO_PuPd,GPIO_Label
PD2.GPIO_Label=input_78
PD2.GPIO_PuPd=GPIO_PULLDOWN
PD2.Signal=GPIO_Input
PD3.GPIOParameters=GPIO_PuPd,GPIO_Label
PD3.GPIO_Label=input_42
PD3.GPIO_PuPd=GPIO_PULLDOWN
PD3.Signal=GPIO_Input
PD4.GPIOParameters=GPIO_PuPd,GPIO_Label
PD4.GPIO_Label=input_79
PD4.GPIO_PuPd=GPIO_PULLDOWN
PD4.Signal=GPIO_Input
PD5.GPIOParameters=GPIO_PuPd,GPIO_Label
PD5.GPIO_Label=input_41
PD5.GPIO_PuPd=GPIO_PULLDOWN
PD5.Signal=GPIO_Input
PD6.GPIOParameters=GPIO_PuPd,GPIO_Label
PD6.GPIO_Label=input_80
PD6.GPIO_PuPd=GPIO_PULLDOWN
PD6.Signal=GPIO_Input
PD7.GPIOParameters=GPIO_PuPd,GPIO_Label
PD7.GPIO_Label=input_20
PD7.GPIO_PuPd=GPIO_PULLDOWN
PD7.Signal=GPIO_Input
PD8.GPIOParameters=GPIO_Label
PD8.GPIO_Label=UART_TX
PD8.Mode=Half_duplex(single_wire_mode)
PD8.Signal=USART3_TX
PD9.GPIOParameters=GPIO_PuPd,GPIO_Label
PD9.GPIO_Label=input_52
PD9.GPIO_PuPd=GPIO_PULLDOWN
PD9.Signal=GPIO_Input
PE0.GPIOParameters=GPIO_PuPd,GPIO_Label
PE0.GPIO_Label=input_25
PE0.GPIO_PuPd=GPIO_PULLDOWN
PE0.Signal=GPIO_Input
PE1.GPIOParameters=GPIO_PuPd,GPIO_Label
PE1.GPIO_Label=input_15
PE1.GPIO_PuPd=GPIO_PULLDOWN
PE1.Signal=GPIO_Input
PE10.GPIOParameters=GPIO_PuPd,GPIO_Label
PE10.GPIO_Label=input_63
PE10.GPIO_PuPd=GPIO_PULLDOWN
PE10.Signal=GPIO_Input
PE11.GPIOParameters=GPIO_PuPd,GPIO_Label
PE11.GPIO_Label=input_57
PE11.GPIO_PuPd=GPIO_PULLDOWN
PE11.Signal=GPIO_Input
PE12.GPIOParameters=GPIO_PuPd,GPIO_Label
PE12.GPIO_Label=input_65
PE12.GPIO_PuPd=GPIO_PULLDOWN
PE12.Signal=GPIO_Input
PE13.GPIOParameters=GPIO_PuPd,GPIO_Label
PE13.GPIO_Label=input_64
PE13.GPIO_PuPd=GPIO_PULLDOWN
PE13.Signal=GPIO_Input
PE14.GPIOParameters=GPIO_PuPd,GPIO_Label
PE14.GPIO_Label=input_55
PE14.GPIO_PuPd=GPIO_PULLDOWN
PE14.Signal=GPIO_Input
PE15.GPIOParameters=GPIO_PuPd,GPIO_Label
PE15.GPIO_Label=input_56
PE15.GPIO_PuPd=GPIO_PULLDOWN
PE15.Signal=GPIO_Input
PE2.GPIOParameters=GPIO_PuPd,GPIO_Label
PE2.GPIO_Label=input_5
PE2.GPIO_PuPd=GPIO_PULLDOWN
PE2.Signal=GPIO_Input
PE3.GPIOParameters=GPIO_PuPd,GPIO_Label
PE3.GPIO_Label=input_37
PE3.GPIO_PuPd=GPIO_PULLDOWN
PE3.Signal=GPIO_Input
PE4.GPIOParameters=GPIO_PuPd,GPIO_Label
PE4.GPIO_Label=input_4
PE4.GPIO_PuPd=GPIO_PULLDOWN
PE4.Signal=GPIO_Input
PE5.GPIOParameters=GPIO_PuPd,GPIO_Label
PE5.GPIO_Label=input_38
PE5.GPIO_PuPd=GPIO_PULLDOWN
PE5.Signal=GPIO_Input
PE6.GPIOParameters=GPIO_PuPd,GPIO_Label
PE6.GPIO_Label=input_26
PE6.GPIO_PuPd=GPIO_PULLDOWN
PE6.Signal=GPIO_Input
PE7.GPIOParameters=GPIO_PuPd,GPIO_Label
PE7.GPIO_Label=input_59
PE7.GPIO_PuPd=GPIO_PULLDOWN
PE7.Signal=GPIO_Input
PE8.GPIOParameters=GPIO_PuPd,GPIO_Label
PE8.GPIO_Label=input_62
PE8.GPIO_PuPd=GPIO_PULLDOWN
PE8.Signal=GPIO_Input
PE9.GPIOParameters=GPIO_PuPd,GPIO_Label
PE9.GPIO_Label=input_58
PE9.GPIO_PuPd=GPIO_PULLDOWN
PE9.Signal=GPIO_Input
PF0.GPIOParameters=GPIO_PuPd,GPIO_Label
PF0.GPIO_Label=input_39
PF0.GPIO_PuPd=GPIO_PULLDOWN
PF0.Signal=GPIO_Input
PF1.GPIOParameters=GPIO_PuPd,GPIO_Label
PF1.GPIO_Label=input_13
PF1.GPIO_PuPd=GPIO_PULLDOWN
PF1.Signal=GPIO_Input
PF10.GPIOParameters=GPIO_PuPd,GPIO_Label
PF10.GPIO_Label=input_10
PF10.GPIO_PuPd=GPIO_PULLDOWN
PF10.Signal=GPIO_Input
PF11.GPIOParameters=GPIO_PuPd,GPIO_Label
PF11.GPIO_Label=input_7
PF11.GPIO_PuPd=GPIO_PULLDOWN
PF11.Signal=GPIO_Input
PF12.GPIOParameters=GPIO_PuPd,GPIO_Label
PF12.GPIO_Label=input_34
PF12.GPIO_PuPd=GPIO_PULLDOWN
PF12.Signal=GPIO_Input
PF13.GPIOParameters=GPIO_PuPd,GPIO_Label
PF13.GPIO_Label=input_6
PF13.GPIO_PuPd=GPIO_PULLDOWN
PF13.Signal=GPIO_Input
PF14.GPIOParameters=GPIO_PuPd,GPIO_Label
PF14.GPIO_Label=input_35
PF14.GPIO_PuPd=GPIO_PULLDOWN
PF14.Signal=GPIO_Input
PF15.GPIOParameters=GPIO_PuPd,GPIO_Label
PF15.GPIO_Label=input_60
PF15.GPIO_PuPd=GPIO_PULLDOWN
PF15.Signal=GPIO_Input
